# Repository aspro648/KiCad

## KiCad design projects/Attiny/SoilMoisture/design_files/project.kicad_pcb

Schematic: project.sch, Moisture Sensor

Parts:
BT1: Battery; BATT_CR2032_SMD
C1: 0.1 uF; C_1206
CON1: ISP; AVR-ISP-6
D0, D1, D2, D3, D4, D5, D6, D7: LED; LED_1206
J1, J2: Conn_01x03; Pin_Header_Straight_1x03_Pitch1.00mm
LS1: Speaker; PS1240_piezo
Probe1, Probe2: Conn_01x01; Pin_Header_Straight_1x01_Pitch2.54mm
Q1: 2N3904; SOT-23
R0, R1, R2, R3, R4, R5, R6, R7, R8: 100; R_1206
R9: 10K; R_1206
SW1: SW_SPDT; SPST_SMD
SW2: SW_Push; SW_SMD_PUSH
U1: ATTINY84A-SSU; SOIC-14_N

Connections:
+BATT: C1.1, CON1.2, SW1.3 (B), U1.1 (VCC)
GND: BT1.2, C1.2, CON1.6, J2.3, LS1.2, R0.2, R1.2, R2.2, R3.2, R4.2, R5.2, R6.2, R7.2, R9.2, SW2.2, U1.14 (GND)
unnamed: BT1.1, SW1.2 (A)
unnamed: CON1.1, D5.2 (A), U1.8 ((PCINT5/DO/MISO/OC1B/ADC5)PA5)
unnamed: CON1.3, D4.2 (A), U1.9 ((PCINT4/USCK/SCL/T1/ADC4)PA4)
unnamed: CON1.4, D7.2 (A), Q1.3 (C), R8.1, U1.7 ((PCINT6/SDA/DI/MOSI/OC1A/ADC6)PA6)
unnamed: CON1.5, U1.4 ((PCINT11/dW/~RESET~)PB3)
unnamed: D0.1 (K), R0.1
unnamed: D0.2 (A), U1.13 ((PCINT0/AREF/ADC0)PA0)
unnamed: D1.1 (K), R1.1
unnamed: D1.2 (A), U1.12 ((PCINT1/AIN0/ADC1)PA1)
unnamed: D2.1 (K), R2.1
unnamed: D2.2 (A), U1.11 ((PCINT2/AIN1/ADC2)PA2)
unnamed: D3.1 (K), R3.1
unnamed: D3.2 (A), U1.10 ((PCINT3/T0/ADC3)PA3)
unnamed: D4.1 (K), R4.1
unnamed: D5.1 (K), R5.1
unnamed: D6.1 (K), R6.1
unnamed: D6.2 (A), U1.2 ((PCINT8/CLKI/XTAL1)PB0)
unnamed: D7.1 (K), R7.1
unnamed: J1.1, Q1.1 (E), R9.1, U1.6 ((PCINT7/ICP/OC0B/ADC7)PA7)
unnamed: J1.2, J1.3, Probe1.1, Q1.2 (B)
unnamed: J2.1, J2.2, Probe2.1, R8.2
unnamed: LS1.1, U1.3 ((PCINT9/XTAL2)PB1)
unnamed: SW2.1, U1.5 ((PCINT10/CKOUT/OC0A/INT0)PB2)

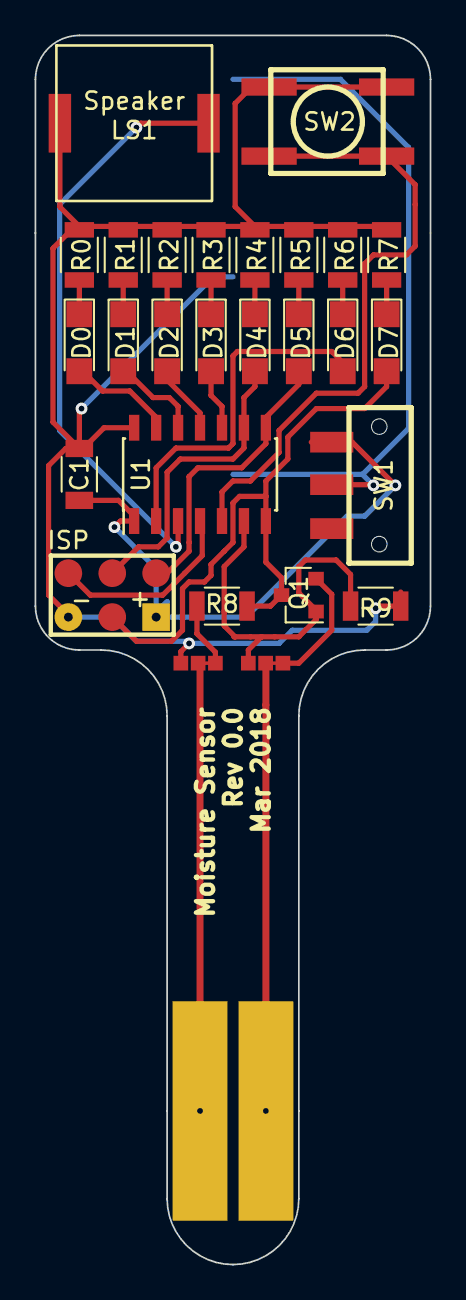
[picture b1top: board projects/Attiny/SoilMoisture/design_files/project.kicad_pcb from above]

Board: 2 copper layers, 22.9 x 71.1 mm, 32 parts (1 on the bottom side), 25 nets.

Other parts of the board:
VAL: MadeInOregonRev25
VAL#2: MB225rev

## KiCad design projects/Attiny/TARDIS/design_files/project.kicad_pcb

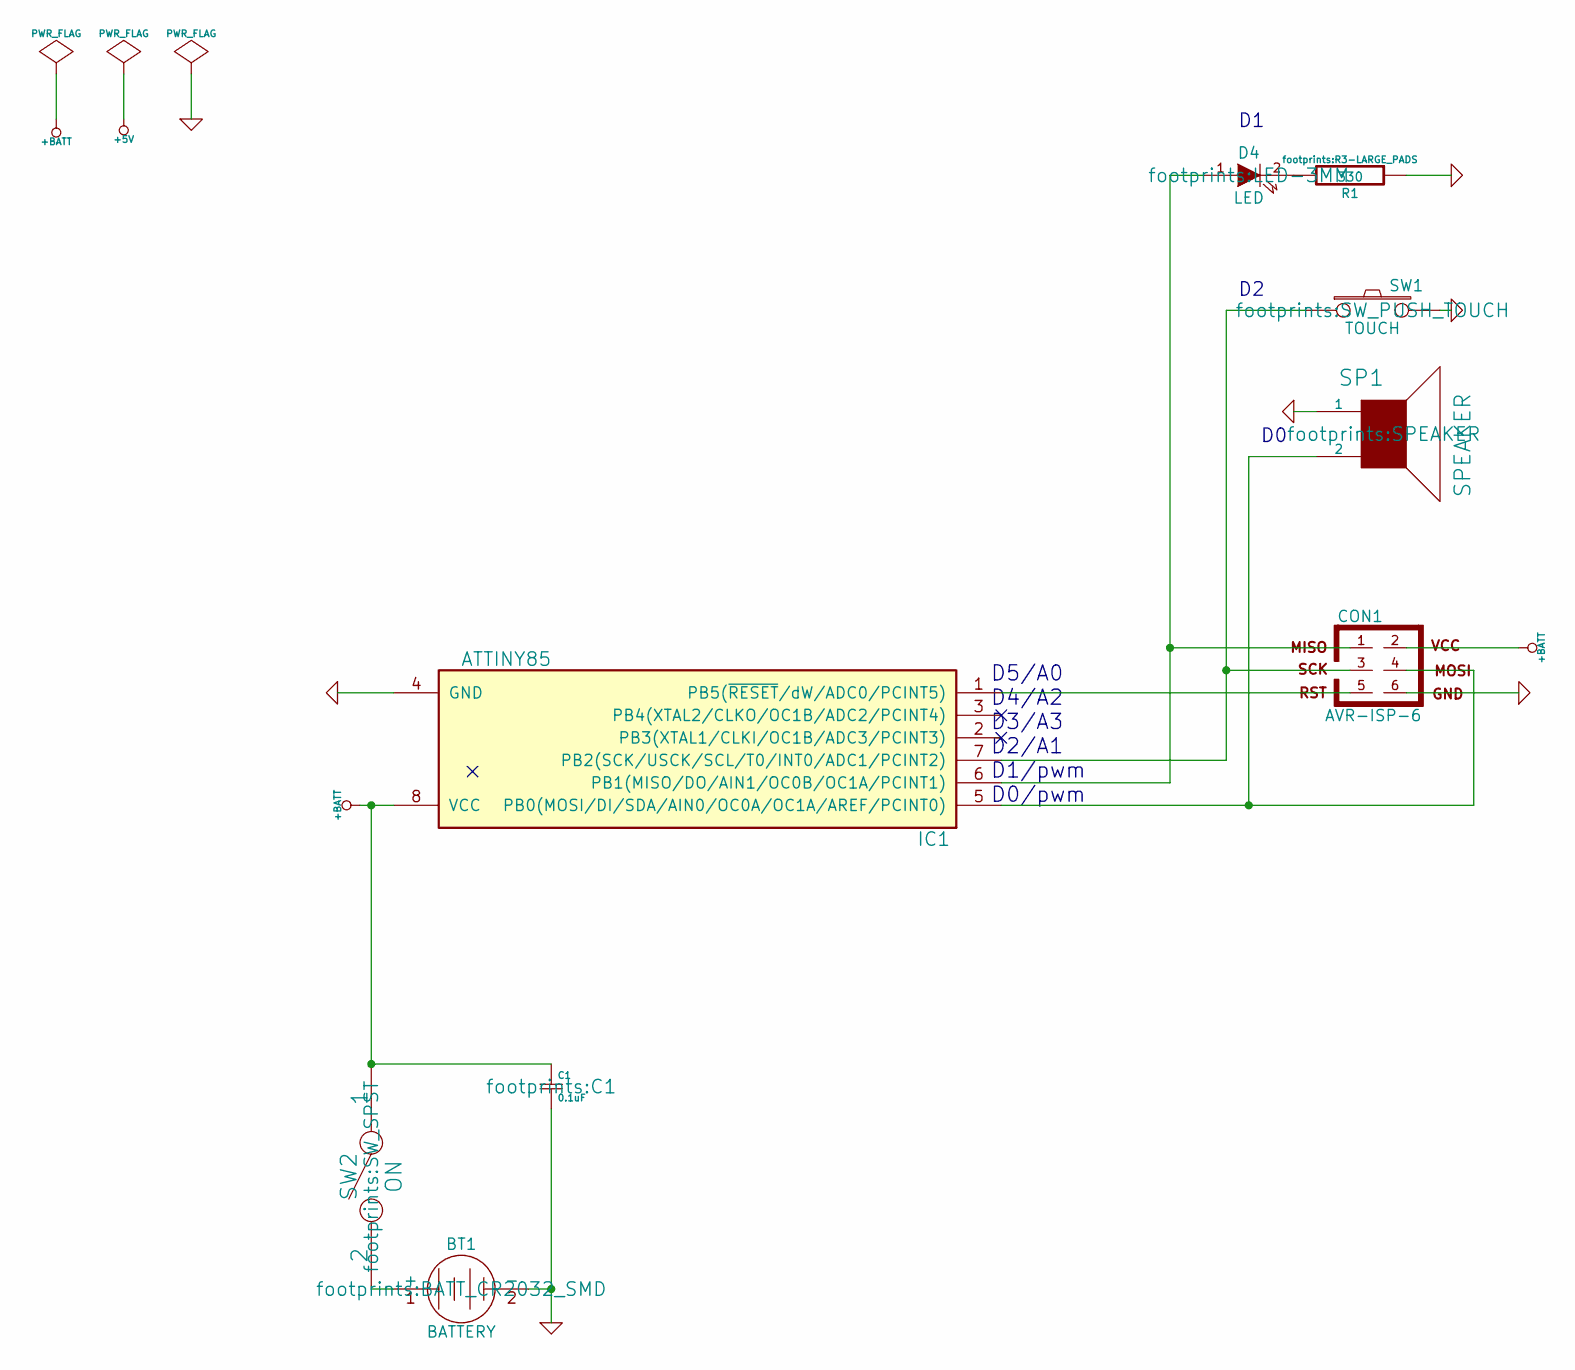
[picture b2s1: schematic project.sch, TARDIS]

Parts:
BT1: BATTERY; BATT_CR2032_SMD
C1: 0.1uF; C1
CON1: AVR-ISP-6; Pin_Header_Straight_2x03_Pitch2.54mm
D4: LED; LED-3MM
IC1: ATTINY85; DIP-8__300
R1: 330; R3-LARGE_PADS
SP1: SPEAKER
SW1: TOUCH; SW_PUSH_TOUCH
SW2: ON; SW_SPST

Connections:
+BATT: C1.1, CON1.2, IC1.8 (VCC), SW2.1
GND: BT1.2 (-), C1.2, CON1.6, IC1.4 (GND), R1.1, SP1.1, SW1.2
unnamed: BT1.1 (+), SW2.2
unnamed: CON1.1, D4.1 (A), IC1.6 (PB1(MISO/DO/AIN1/OC0B/OC1A/PCINT1))
unnamed: CON1.3, IC1.7 (PB2(SCK/USCK/SCL/T0/INT0/ADC1/PCINT2)), SW1.1
unnamed: CON1.4, IC1.5 (PB0(MOSI/DI/SDA/AIN0/OC0A/OC1A/AREF/PCI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), SP1.2
unnamed: CON1.5, IC1.1 (PB5(~RESET~/dW/ADC0/PCINT5))
unnamed: D4.2 (K), R1.2

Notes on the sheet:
D5/A0 D4/A2 D3/A3 D2/A1 D1/pwm D0/pwm

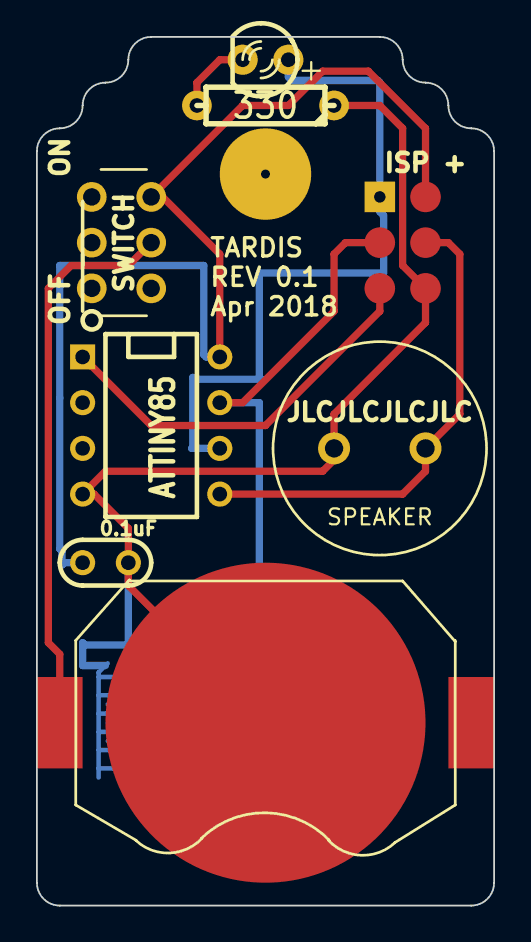
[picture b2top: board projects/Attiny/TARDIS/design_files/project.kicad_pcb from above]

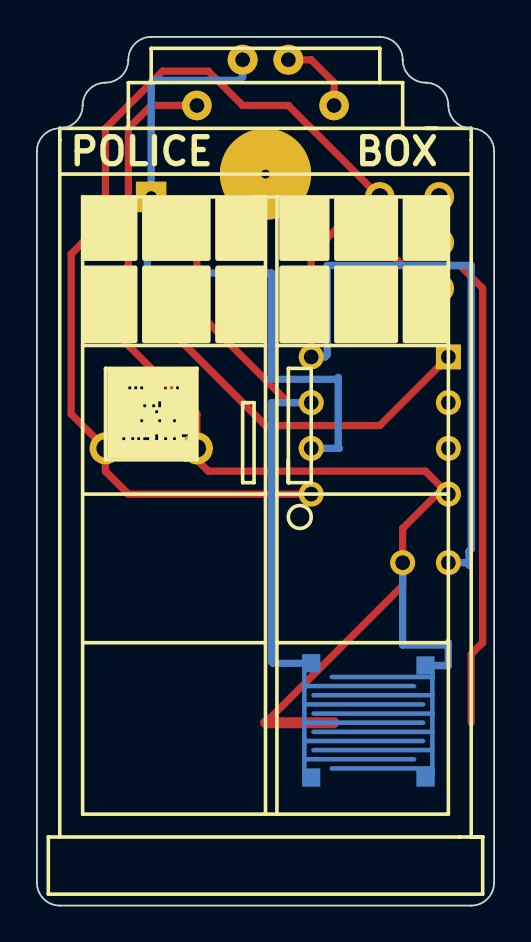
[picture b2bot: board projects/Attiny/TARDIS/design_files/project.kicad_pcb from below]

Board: 2 copper layers, 25.4 x 48.3 mm, 11 parts (2 on the bottom side), 8 nets.

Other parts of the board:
HOLE_2: CONN_1; 078hole
LOGO: sign

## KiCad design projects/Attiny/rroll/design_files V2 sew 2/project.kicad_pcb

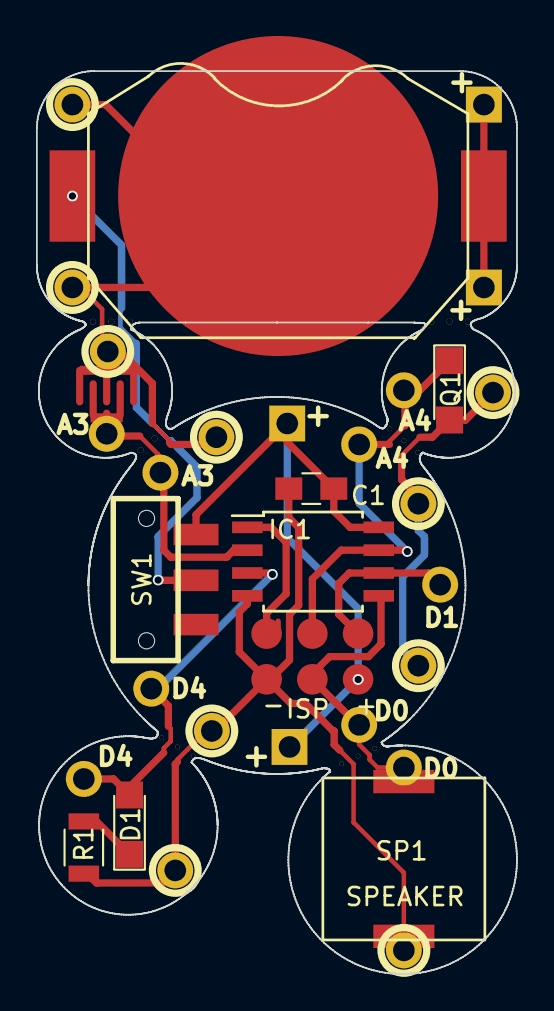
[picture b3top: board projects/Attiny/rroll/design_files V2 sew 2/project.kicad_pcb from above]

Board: 2 copper layers, 26.7 x 50.2 mm, 33 parts (0 on the bottom side), 10 nets.

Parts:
BT1: Battery; BATT_CR2032_SMD
C1: 0.1 uF; C_0805_HandSoldering
CON1: ISP; Pin_Header_Straight_2x03_Pitch2.54mm
D1: LED; LED_1206
IC1: ATTINY85; SOIJ-8_5.3x5.3mm_Pitch1.27mm
J1: JMP; SW_SMD_TOUCH
P2, P3, P5, P6, P7: CONN_01X01; Pad_sew
P4: CONN_01X01; Pad_Ground
P8: CONN_01X01; Pad_Pos
PA1: CONN_01X01; Pad_sew
PA2: CONN_01X01; Pad_Ground
PB1, PB2: CONN_01X01; Pad_Pos
PB3, PB4: CONN_01X01; Pad_Ground
PG1, PG2, PG3: CONN_01X01; Pad_Ground
PL1: CONN_01X01; Pad_sew
PL2: CONN_01X01; Pad_Ground
PP1: CONN_01X01; Pad_Pos
PS1: CONN_01X01; Pad_sew
PS2: CONN_01X01; Pad_Ground
PT1: CONN_01X01; Pad_sew
PT2: CONN_01X01; Pad_Ground
Q1: LIGHT; LED_1206
R1: 330; R_1206
SP1: SPEAKER; PS1240_piezo
SW1: SW_SPDT; SPST_SMD

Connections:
+BATT: BT1.1, PB1.1, PB2.1, SW1.2
/D3: IC1.2, J1.2, P2.1, PA1.1
/D4: D1.2, IC1.3, P3.1, PL1.1
/MISO: CON1.1, IC1.6, P6.1
/MOSI: CON1.4, IC1.5, P5.1, PS1.1, SP1.2
/RST: CON1.5, IC1.1
/SCK: CON1.3, IC1.7, P7.1, PT1.1, Q1.1
/VCC: C1.2, CON1.2, IC1.8, P8.1, PP1.1, SW1.1
GND: BT1.2, C1.1, CON1.6, IC1.4, J1.1, P4.1, PA2.1, PB3.1, PB4.1, PG1.1, PG2.1, PG3.1, PL2.1, PS2.1, PT2.1, Q1.2, R1.1, SP1.1
unnamed: D1.1, R1.2

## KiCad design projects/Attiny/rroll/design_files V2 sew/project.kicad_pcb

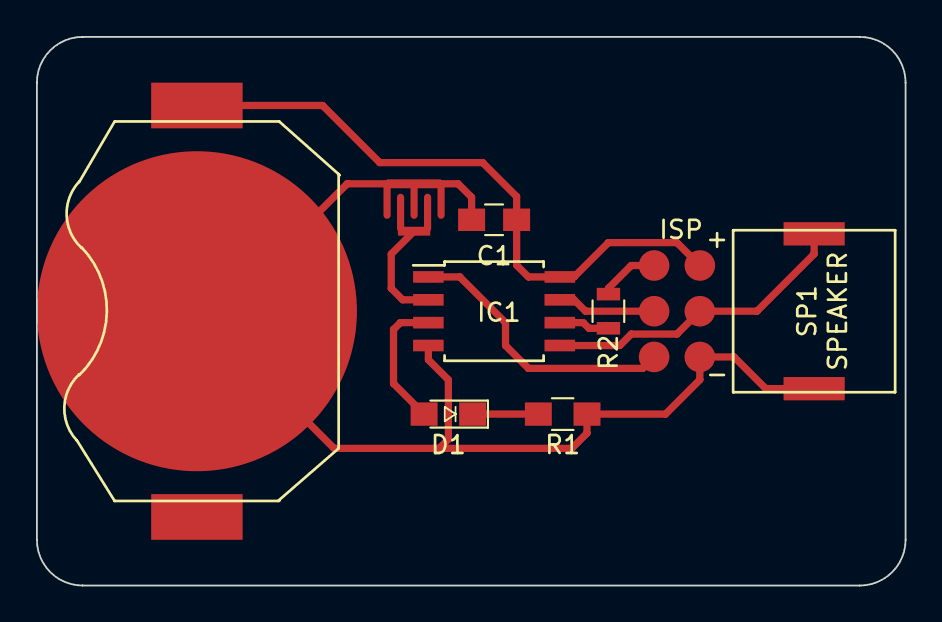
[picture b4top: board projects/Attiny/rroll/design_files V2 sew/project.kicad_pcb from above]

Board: 2 copper layers, 48.3 x 30.5 mm, 9 parts (0 on the bottom side), 10 nets.

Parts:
BT1: Battery; BATT_CR2032_SMD
C1: 0.1 uF; C_0805_HandSoldering
CON1: ISP; Pin_Header_Straight_2x03_Pitch2.54mm
D1: LED; LED_0805_HandSoldering
IC1: ATTINY85; SOIJ-8_5.3x5.3mm_Pitch1.27mm
J1: JMP; SW_SMD_TOUCH
R1: 330; R_0805_HandSoldering
R2: 0; R_0805
SP1: SPEAKER; PS1240_piezo

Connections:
+BATT: BT1.1, C1.2, CON1.2, IC1.8
/D3: IC1.2, J1.2
/D4: D1.2, IC1.3
/MISO: IC1.6, R2.2
/MOSI: CON1.4, IC1.5, SP1.2
/RST: CON1.5, IC1.1
/SCK: CON1.3, IC1.7
GND: BT1.2, C1.1, CON1.6, IC1.4, J1.1, R1.1, SP1.1
unnamed: CON1.1, R2.1
unnamed: D1.1, R1.2

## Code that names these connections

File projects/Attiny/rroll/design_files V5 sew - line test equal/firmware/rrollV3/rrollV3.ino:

/*
Heartbeat code based on Emily Lovell's LilyTiny:
http://dlnmh9ip6v2uc.cloudfront.net/datasheets/E-Textiles/Lilypad/LilyTiny.ino
https://users.soe.ucsc.edu/~emme/

Arduino pinout development based on FunShield:
https://www.tindie.com/products/MakersBox/funshield-arduino-shield-kit/

Not all Attiny cores support the tone() function. Try this one
https://github.com/SpenceKonde/ATTinyCore

ATMEL ATTINY45/85 Pin Assignments
                   +-\/-+
  Ain0 (D 5) PB5  1|    |8  Vcc
  Ain3 (D 3) PB3  2|    |7  PB2 (D 2) Ain1
  Ain2 (D 4) PB4  3|    |6  PB1 (D 1) pwm1
             GND  4|    |5  PB0 (D 0) pwm0

cd C:\Users\Maker's Box\Documents\arduino-1.6.4\hardware\tools\avr\bin
avrdude -C ..\etc\avrdude.conf -P COM12 -b 19200 -c avrisp -p attiny25 -v -e -U lfuse:w:0xE2:m -U hfuse:w:0xD7:m -U efuse:w:0xFf:m  -U flash:w:ICanSMDv25.hex


*/


int ledPin = 4;  // assume negative lead
int touchPin = 3;

int on_time = 10;  // in seconds


void setup(){

  // test: with a weak pullup, the pin will read HIGH if LED in backward (no path for current)
  pinMode(touchPin, INPUT);
  digitalWrite(touchPin, HIGH);
  
  pinMode(ledPin, OUTPUT);

}


void loop(){
  if(0){
    int val = 1000;
    if(checkTouch()){
      val = 100;
    }
    digitalWrite(ledPin, HIGH);
    delay(val);
    digitalWrite(ledPin, LOW);
    delay(val);
  }

  heartBeat(on_time);
}


bool checkTouch(){
  int val = analogRead(touchPin);
  if (val < 1000){
    return true;
  }
  return false;
}

boolean heartBeat(int on_time){
  // based on http://dlnmh9ip6v2uc.cloudfront.net/datasheets/E-Textiles/Lilypad/LilyTiny.ino

  // Variables and constants for fading pin. Needs to be a hardware PWM pin; on
  byte heartStage = 0;
  int heartBrightness = 0;
  byte heartCounter = 0;
  long off_time = millis() + on_time * 1000;

  while(millis() < off_time){
    delayMicroseconds(9999);
    // calculate brightness for heartbeat pin (by cycling 
    // through phases of pulse pattern)
    heartCounter++;
    if (heartCounter > 144) {
      heartStage = (heartStage + 1) % 4;
      heartCounter = 0;
    }
    else {
      if(checkTouch()){
        analogWrite(ledPin, heartBrightness);
      }
      else{
        digitalWrite(ledPin, LOW);
      }
      switch(heartStage) {
        case 0:         
          heartCounter += 144/12.0;
          heartBrightness += 255/12.0;
          if (heartBrightness > 255)
            heartBrightness = 255;
          break;
        case 1:
          heartCounter += 144/24.0;
          heartBrightness -= 255/24.0;
          if (heartBrightness < 0)
            heartBrightness = 0;
          break;
        case 2:
          heartCounter += 144/12.0;
          heartBrightness += 255/12.0;
          if (heartBrightness > 255)
            heartBrightness = 255;
          break;
        case 3:
          heartCounter += 144/72.0;
          heartBrightness -= 255/72.0;
          if (heartBrightness < 0)
            heartBrightness = 0;
          break;
      }//switch
    }//else
    
  }
  
  return(true);
}

/*

void blinks(int val){
  int msd = 1000;
  bool fsd = false;
  if (val == 0){
    blink(50);
  }
  else{
    while(msd > 0){
      int digit = val / msd;
      if (digit > 0){
        fsd = true; 
      }
      if (digit == 0 && fsd){
        blink(50);
      }
      for(int x=0; x < digit; x++){
        blink(500);
      }
      delay(1000); 
      val = val - msd * digit;  
      msd = msd / 10;  
    }
  }
}


void blink(int val){
  digitalWrite(ledPinPos, HIGH);
  delay(val);
  digitalWrite(ledPinPos, LOW);
  delay(val);
}

*/
